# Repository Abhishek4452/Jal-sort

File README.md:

# Jal-sort
kicad schematic of the jal sort (water source )

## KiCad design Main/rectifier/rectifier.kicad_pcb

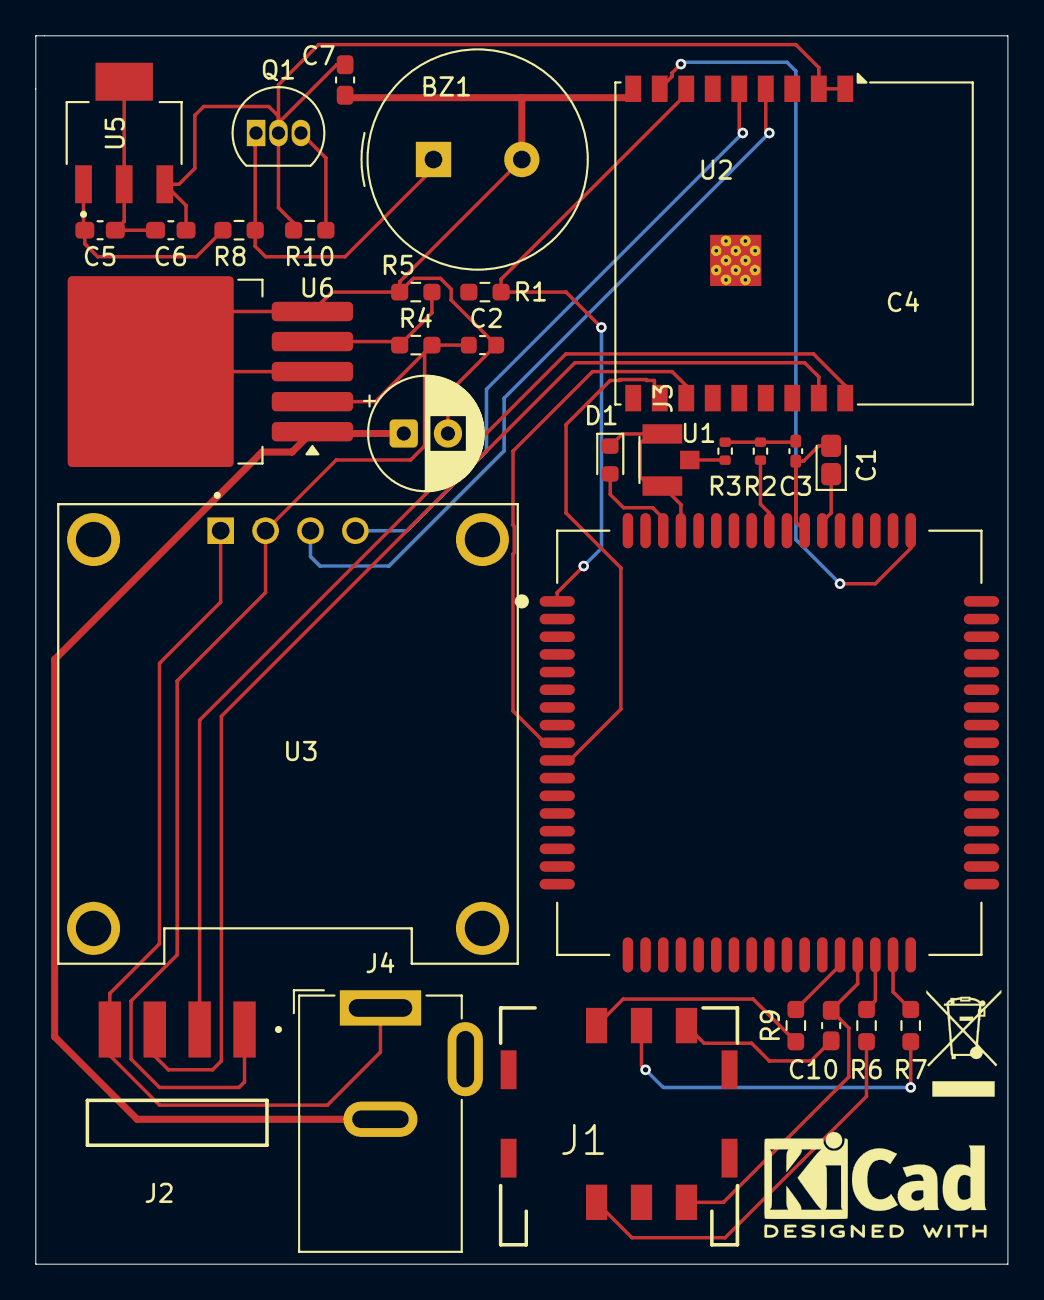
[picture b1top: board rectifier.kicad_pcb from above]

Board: 2 copper layers, 55.0 x 69.5 mm, 30 parts (0 on the bottom side), 26 nets.

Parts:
BZ1: Buzzer; Buzzer_TDK_PS1240P02BT_D12.2mm_H6.5mm
C1: 0.1uf; CP_EIA-1608-08_AVX-J_HandSolder
C2: 100uf; C_0603_1608Metric
C3: C; C_0402_1005Metric_Pad0.74x0.62mm_HandSolder
C4: 470uf; CP_Radial_D6.3mm_P2.50mm
C5: 0.47uF; C_0603_1608Metric_Pad1.08x0.95mm_HandSolder
C6: 33uf; C_0603_1608Metric_Pad1.08x0.95mm_HandSolder
C7: 33uF; C_0603_1608Metric_Pad1.08x0.95mm_HandSolder
C10: 100nf; C_0603_1608Metric_Pad1.08x0.95mm_HandSolder
D1: status LEd; LED_0603_1608Metric
J1: SIM7050-6-0-00-X_REVC; GCT_SIM7050-6-0-00-X_REVC
J2: TSM-104-01-TM-SH; SAMTEC_TSM-104-01-TM-SH
J3: U.FL-R-SMT_01_; HRS_U.FL-R-SMT_01_
J4: Jack-DC; BarrelJack_GCT_DCJ200-10-A_Horizontal
Q1: BS170; TO-92_Inline
R1: 10k ohm; R_0603_1608Metric_Pad0.98x0.95mm_HandSolder
R2, R3: R; R_0402_1005Metric
R4: 6.8k ohm; R_0603_1608Metric_Pad0.98x0.95mm_HandSolder
R5: 2.2k ohm; R_0603_1608Metric_Pad0.98x0.95mm_HandSolder
R6, R7, R9: 22 ohm; R_0603_1608Metric_Pad0.98x0.95mm_HandSolder
R8, R10: 4.7K; R_0603_1608Metric_Pad0.98x0.95mm_HandSolder
U1: SIM7000E; SIMCON_SIM7000E
U2: ESP32-C3-WROOM-02
U3: DM-OLED096-636; MODULE_DM-OLED096-636
U5: LM3940IMP-3.3; SOT230P700X180-4N
U6: LM2596S-5; TO-263-5_TabPin3

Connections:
+3.3V: C6.1, C7.1, Q1.2 (G), R1.1, R10.1, U2.1 (3V3), U2.2 (EN), U5.3 (OUT)
+5V: C1.1, C2.1, C5.1, J2.01, R4.1, R8.1, U1.55 (VBAT), U1.56 (VBAT), U1.57 (VBAT), U3.2 (VCC_IN), U5.1 (IN), U6.2 (OUT)
+9V: C4.1, J4.2, U6.1 (VIN)
/BUZZER: BZ1.1 (+), Q1.1 (D), R8.2
/ECHO: J2.03, U2.17 (IO1)
/ESP 32_TO_BUZZER: Q1.3 (S), R10.2, U2.15 (IO3)
/NET_STATUS: U1.52 (NETLIGHT), U2.8 (IO9)
/PWR_KEY_SIM: R1.2, U1.1 (~PWRKEY), U2.7 (IO8)
/RF_ANTENNA: R2.2, U1.60 (RF_ANT)
/RX: U1.10 (RXD), U2.11 (IO20/RXD)
/SCL_OLED: U2.4 (IO5), U3.3 (SCL)
/SDA_OLED: U2.5 (IO6), U3.4 (SDA)
/SIM Card CLK: R6.2, U1.32 (SIM_CLK)
/SIM Card RST: R7.2, U1.33 (SIM_RST)
/SIM_DATA: C10.1, J1.C1 (VCC), U1.31 (SIM_DATA)
/SIM_MODULE_STATUS: D1.2 (A), U1.66 (STATUS)
/SIM_VDD: R9.2, U1.30 (SIM_VDD)
/TRIGGER: J2.02, U2.18 (IO0)
/TX: U1.9 (TXD), U2.12 (IO21/TXD)
GND: BZ1.2 (-), C1.2, C2.2, C3.2, C4.2, C5.2, C6.2, C7.2, C10.2, D1.1 (K), J1.C5 (GND), J2.04, J3.1 (GND), J3.2 (GND), J4.1, R5.2, U1.2 (GND), U1.17 (GND), U1.18 (GND), U1.29 (GND), U1.39 (GND), U1.45 (GND), U1.46 (GND), U1.54 (GND), U1.58 (GND), U1.59 (GND), U1.61 (GND), U1.62 (GND), U1.63 (GND), U1.64 (GND), U1.65 (GND), U2.9 (GND), U2.19 (GND), U3.1 (GND), U5.2 (GND), U5.4 (GND), U6.3 (GND), U6.5 (~ON/OFF)
unnamed: C3.1, R2.1, R3.2
unnamed: J1.C3 (CLK), R6.1
unnamed: J1.C7 (I/O), R9.1
unnamed: J1.C6 (VPP), R7.1
unnamed: J3.3 (SIG), R3.1
unnamed: R4.2, R5.1, U6.4 (FB)

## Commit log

2026-03-28 adding my complete documentation of kicad-9
2026-03-29 adding sim module to the schematic
2026-04-07 making connection for SIM modeule
2026-04-23 updated schematic
2026-04-26 version 1 complete
2026-04-26 pic_update
